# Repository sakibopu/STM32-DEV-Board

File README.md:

# STM32 DEV Board
 STM32 DEV Board

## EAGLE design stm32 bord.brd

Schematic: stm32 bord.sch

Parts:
C1, C5, C6, C7, C8: 104p; _0603
C2: 105p; _0603
C3, C4: 10uF; _0603
C9, C10, C11, C12: 20p; _0603
IC1: REG1118; SOT223
J1: USB3090-XX-X_REVE; GCT_USB3090-XX-X_REVE
JP1: PINHD-2X3; 2X03
JP2, JP3: PINHD-1X20; 1X20
LED1, LED2: LED0603; CHIPLED_0603
R1: 510r; 0603
R2: 10K; 0603
R3, R4: 100K; 0603
R5: 510R; 0603
R6: 229R; 0603
R7, R8: 20R; 0603
R9: 1M; 0603
SW1: SWITCH_PUSHBUTTONSOFTTOUCHSMD_SJ; PUSHBUTTON_SMD_SJ
SWD: PINHD-1X4; 1X04
U1: STM32F103C8T6; QFP50P900X900X160-48N
Y1: 8MHz; CRYSTAL-SMD-2X6-CYL
Y2: 32.768kHz; CRYSTAL-SMD-2X6-CYL

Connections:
3.3V: C1.1, C3.1, C5.1, C6.1, C7.1, C8.1, IC1.1 (VOUT), JP1.1, JP1.2, JP2.18, JP3.1, LED1.A, LED2.A, R2.2, SWD.1, U1.8 (VSSA), U1.9 (VDDA), U1.24 (VDD), U1.36 (VDD), U1.48 (VDD)
+5V: C4.1, IC1.3 (VIN), J1.1 (VBUS), JP3.3, R6.2
BOOT0: R3.2, U1.44 (BOOT0)
BOOT1: R4.1, U1.20 (PB2)
GND: C1.2, C2.2, C3.2, C4.2, C5.2, C6.2, C7.2, C8.2, C9.2, C10.2, C11.2, C12.2, IC1.2 (GND), J1.4 (ID), J1.5 (GND), J1.6 (SHIELD), J1.7 (SHIELD), J1.8 (SHIELD), J1.9 (SHIELD), JP1.5, JP1.6, JP2.19, JP2.20, JP3.2, R1.1, R6.1, SW1.P$1, SWD.4, U1.23 (VSS), U1.35 (VSS), U1.47 (VSS)
unnamed: JP1.3, R3.1
unnamed: JP1.4, R4.2
unnamed: LED1.C, R1.2
unnamed: LED2.C, R5.2
unnamed: J1.2 (D-), R7.2
unnamed: J1.3 (D+), R8.2
NRST: JP2.17
OSCIN: C11.1, R9.2, U1.5 (PD0_OSC_IN), Y1.X2 (2)
OSCOUT: C12.1, R9.1, U1.6 (PD1_OSC_OUT), Y1.X1 (1)
PA0: JP2.5, U1.10 (PA0_WKUP)
PA1: JP2.6, U1.11 (PA1)
PA2: JP2.7, U1.12 (PA2)
PA3: JP2.8, U1.13 (PA3)
PA4: JP2.9, U1.14 (PA4)
PA5: JP2.10, U1.15 (PA5)
PA6: JP2.11, U1.16 (PA6)
PA7: JP2.12, U1.17 (PA7)
PA8: JP3.16, U1.29 (PA8)
PA9: JP3.15, U1.30 (PA9)
PA10: JP3.14, U1.31 (PA10)
PA11: JP3.13, R7.1, U1.32 (PA11)
PA12: JP3.12, R8.1, U1.33 (PA12)
PA13: U1.34 (PA13)
PA14: U1.37 (PA14)
PA15: JP3.11, U1.38 (PA15)
PB0: JP2.13, U1.18 (PB0)
PB1: JP2.14, U1.19 (PB1)
PB3: JP3.10, U1.39 (PB3)
PB4: JP3.9, U1.40 (PB4)
PB5: JP3.8, U1.41 (PB5)
PB6: JP3.7, U1.42 (PB6)
PB7: JP3.6, U1.43 (PB7)
PB8: JP3.5, U1.45 (PB8)
PB9: JP3.4, U1.46 (PB9)
PB10: JP2.15, U1.21 (PB10)
PB11: JP2.16, U1.22 (PB11)
PB12: JP3.20, U1.25 (PB12)
PB13: JP3.19, U1.26 (PB13)
PB14: JP3.18, U1.27 (PB14)
PB15: JP3.17, U1.28 (PB15)
PC13: JP2.2, R5.1, U1.2 (PC13-TAMPER-RTC)
PC14: C9.1, JP2.3, U1.3 (PC14-OSC32_IN), Y2.X2 (2)
PC15: C10.1, JP2.4, U1.4 (PC15-OSC32_OUT), Y2.X1 (1)
RESET: C2.1, R2.1, SW1.P$2, U1.7 (NRST)
SWCLK: SWD.3
SWDIO: SWD.2
VBAT: JP2.1, U1.1 (VBAT)

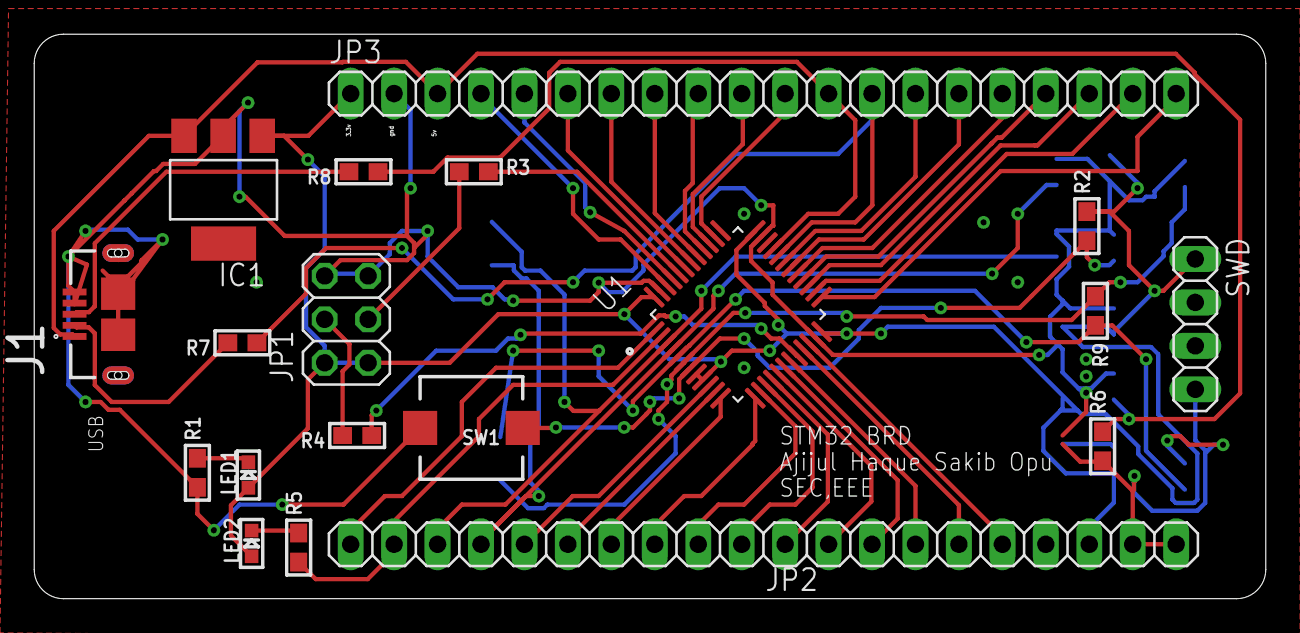
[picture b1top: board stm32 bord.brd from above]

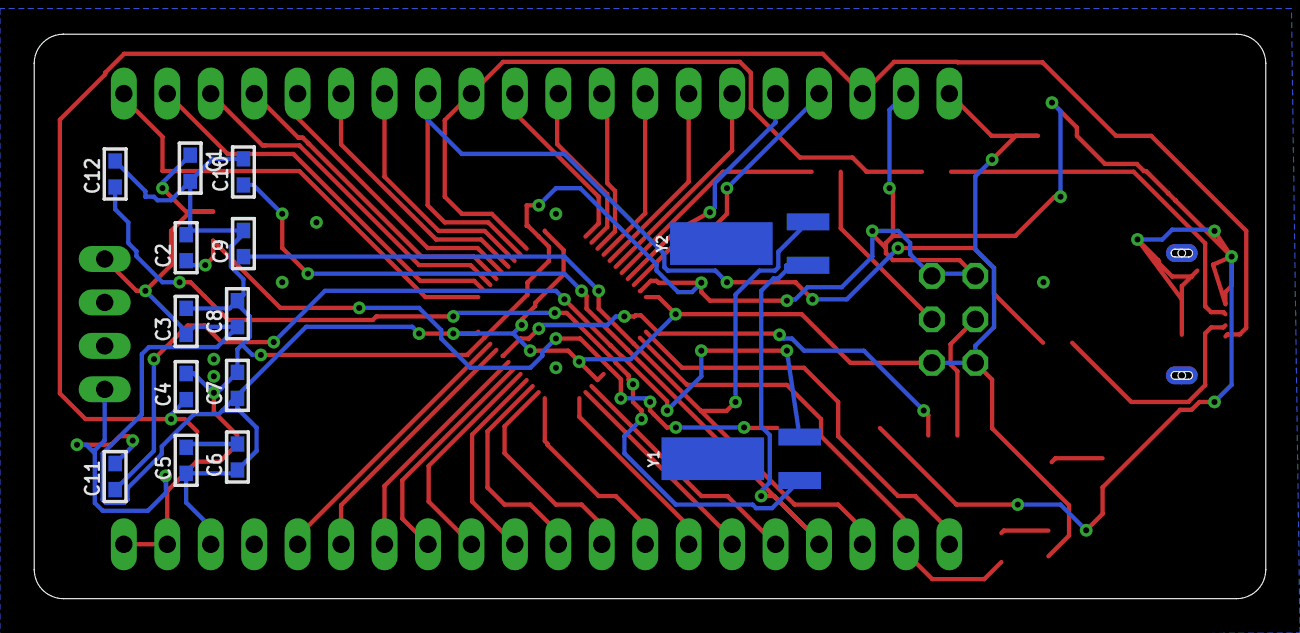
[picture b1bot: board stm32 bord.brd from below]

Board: 2 copper layers, 72.0 x 33.0 mm, 33 parts (14 on the bottom side), 47 nets.

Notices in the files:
parts and their libraries:
microbuilder: This work is placed in the public domain, and may be freely used for commercial and non-commercial work with the following conditions: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
SparkFun-Clocks: Licensing: Creative Commons ShareAlike 4.0 International - https://creativecommons.org/licenses/by-sa/4.0
